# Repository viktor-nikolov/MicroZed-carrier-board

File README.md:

# MicroZed development carrier board

This repository provides KiCad design and production files for a [MicroZed](https://www.avnet.com/wps/portal/us/products/avnet-boards/avnet-board-families/microzed/) development carrier board (a.k.a. MicroZed carrier card).

### Please see [the repository's Wiki](https://github.com/viktor-nikolov/MicroZed-carrier-board/wiki) for details.

You are welcome to leave feedback in [the discussion](https://github.com/viktor-nikolov/MicroZed-carrier-board/discussions).

#### List of features:

- 106 digital I/O pins exposed via female headers
  
  - 16 I/O pins work on 5 V (exposed via two PMOD headers), and the rest of the pins work on 3.3 V

- 2 dedicated analog input pins XADC VP/VN

- 2 LEDs

- 2 push buttons

- 50 MHz precision oscillator (intended as an external clock input to the FPGA Programmable Logic)

- UART to USB conversion chip with the micro-USB connector (intended to enable UART communication for the FPGA Programmable Logic)

- Power input via micro-USB connector or screw terminal. On board power switch.

- Compatible with both [MicroZed 7010](https://www.avnet.com/shop/us/products/avnet-engineering-services/aes-z7mb-7z010-som-g-rev-h-3074457345644698173/?INTCMP=AMER-ECOMM-AVNET-BOARDS-AVT-INT-WEB-MICROZED-PRODUCTS-08282021) and [MicroZed 7020](https://www.avnet.com/shop/us/products/avnet-engineering-services/aes-z7mb-7z020-som-g-rev-h-3074457345644698177/?INTCMP=AMER-ECOMM-AVNET-BOARDS-AVT-INT-WEB-MICROZED-PRODUCTS-08282021).

&nbsp;

See other photos [here](pictures).

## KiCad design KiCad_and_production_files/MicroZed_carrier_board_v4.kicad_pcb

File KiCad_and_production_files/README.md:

# KiCad design files and production files

### Please see [the repository's Wiki](https://github.com/viktor-nikolov/MicroZed-carrier-board/wiki/1.-Board-design) for details.

I designed the board in [KiCad 7.0](https://www.kicad.org/).

> [!IMPORTANT]
> 
> I designed the board from the very beginning with the intention to manufacture it using [JLCPCB Manufacturing and Assembly](https://jlcpcb.com/capabilities/pcb-assembly-capabilities). (I'm not affiliated with JLCPCB in any way. I'm just their customer. :smiley:). The production files in this repository are ready for ordering manufacturing and assembly from JLCPCB. 
> 
> The manufacture of this board is not exactly cheap. Production of the final revision of the board (2 assembled boards + 3 spare PCBs) cost me $194 + shipping costs. (However you can save $33 if you exclude the [50 MHz oscillator X1](https://jlcpcb.com/partdetail/Xtaltq-NT0503DH3I507BN50/C2920832) from the assembly.)
> 
> My selection of parts was dictated by the availability of suitable parts in the [JLCPCB Assembly Parts Library](http://jlcpcb.com/parts) as of August 2023.
> 
> Some parts are tiny and have pads on the bottom. You would need a reflow oven or a hot plate for DIY assembly.

See the [list of all parts](MicroZed_carrier_board_v4_parts.pdf) used in the design (also provided as [an Excel file](MicroZed_carrier_board_v4_parts.xlsx))

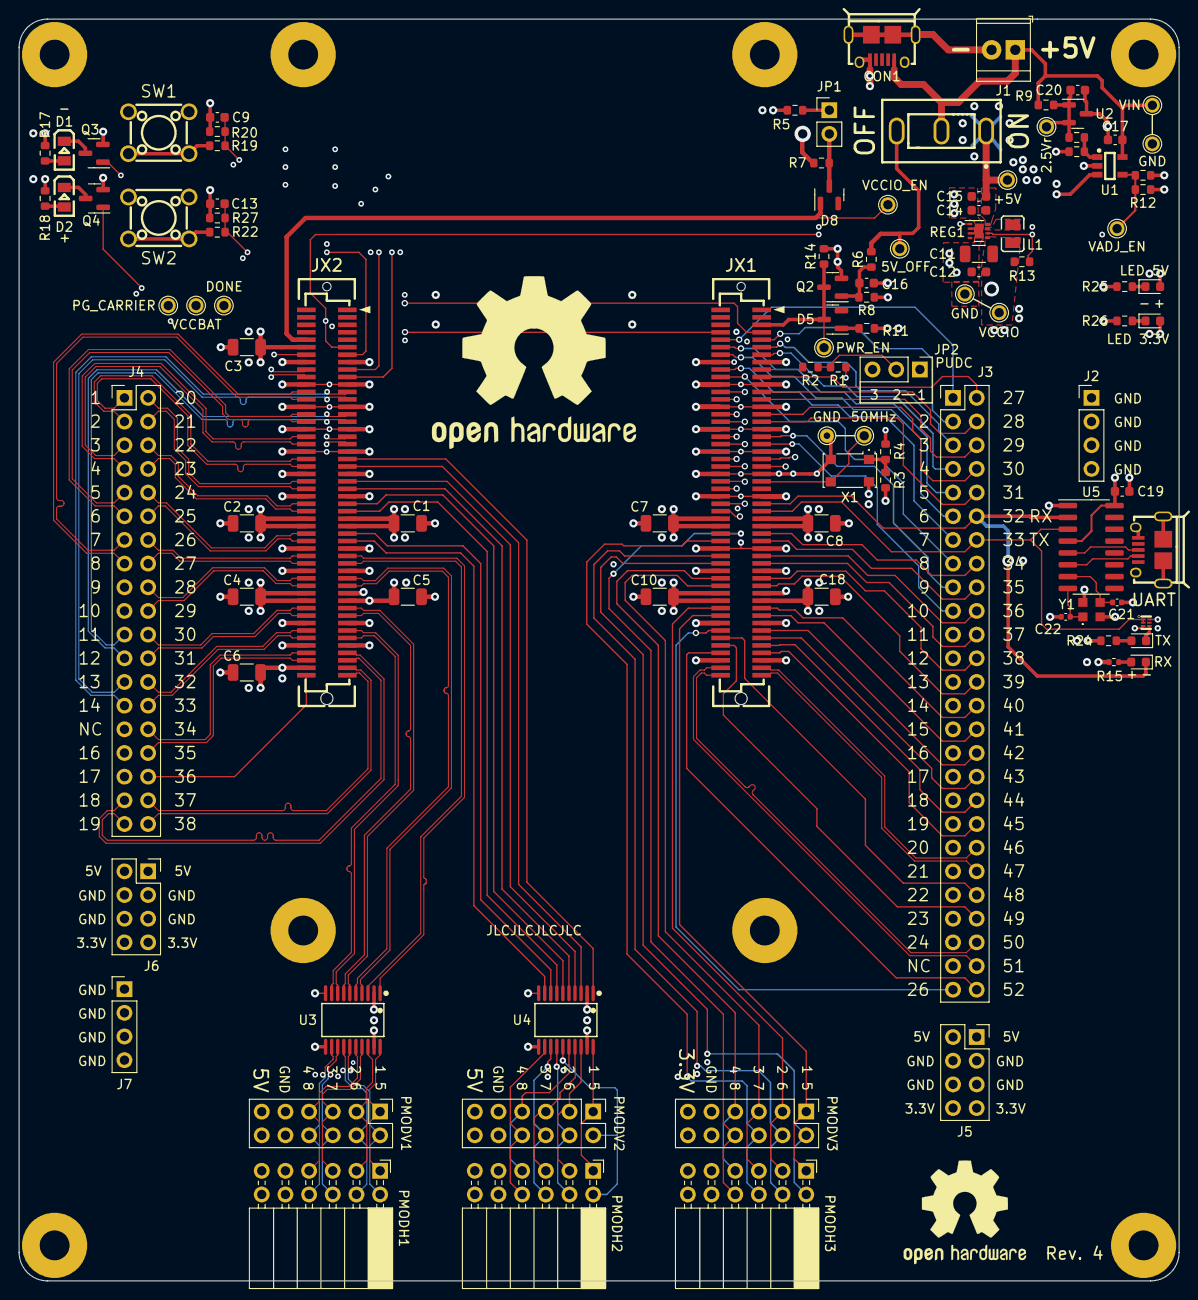
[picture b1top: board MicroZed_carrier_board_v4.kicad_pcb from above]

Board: 6 copper layers, 124.5 x 135.4 mm, 116 parts (0 on the bottom side), 169 nets.

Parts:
C1, C11: 22uF 10V; C_1206_3216Metric
C2, C3, C4, C5, C6, C7, C8, C10, C18: 22uF; C_1206_3216Metric
C9, C12, C13, C15, C16, C17, C19, C20: 100nF; C_0603_1608Metric
C14: 10uF 10V; C_0603_1608Metric
C21, C22: 22pF; C_0402_1005Metric
CON1: USB_B_Micro; MICRO-USB-SMD_HRS-ZX62D-B-5P830
CON2: UART; MICRO-USB-SMD_HRS-ZX62D-B-5P830
D1, D2: LED yellow; LED0805
D3, D4: LED green; LED_0603_1608Metric
D5, D8: BAT54C; SOT-23
D6: RX; LED_0603_1608Metric
D7: TX; LED_0603_1608Metric
H1, H2, H3, H4, H5, H6, H7, H8: MountingHole_3.2mm_Pad_7mm
J1: Screw_Terminal_01x02; TerminalBlock_TE_282834-2_1x02_P2.54mm_Horizontal
J2, J7: GND header for probes; PinHeader_1x04_P2.54mm_Vertical
J3: Conn_02x26_Top_Bottom; PinSocket_2x26_P2.54mm_Top_Bottom_nums
J4: Conn_02x19_Top_Bottom; PinSocket_2x19_P2.54mm_Top_Bottom_nums
J5, J6: Power Connector; PinSocket_2x04_P2.54mm_Vertical
JP1: Jumper_2_Open; PinHeader_1x02_P2.54mm_Vertical
JP2: PUDC selection; PinHeader_1x03_P2.54mm_Vertical
JX1, JX2: BergStak-100pos-plug-61083-101400
L1: 1uH 2A; Inductor-0806_L2.0-W1.6-1
OSHW-Logo: OSHW-Logo2_14.6x12mm_SilkScreen
OpenHW logo: OSHW-Logo2_24.3x20mm_SilkScreen
PMODH1, PMODH2, PMODH3: PMOD_Socket_Horizontal
PMODV1, PMODV2, PMODV3: PMOD_Socket_Vertical
Q2, Q3, Q4: BSS138; SOT-23
R1, R5, R6, R9: 1K; R_0603_1608Metric
R2, R19, R22: 100R; R_0603_1608Metric
R3: 220R 1%; R_0603_1608Metric
R4: 300R 1%; R_0603_1608Metric
R7: 10K; R_0603_1608Metric
R8: 3K92 1%; R_0603_1608Metric
R10: 1K5 1%; R_0603_1608Metric
R11, R16: 680R 1%; R_0603_1608Metric
R12: 3K; R_0603_1608Metric
R13: 180k; R_0603_1608Metric
R14: 430R 1%; R_0603_1608Metric
R15: 133R; R_0402_1005Metric
R17, R18: 150R; R_0603_1608Metric
R20, R27: 3K3; R_0603_1608Metric
R23: 100K; R_0603_1608Metric
R24: 154R; R_0603_1608Metric
R25: 4K87; R_0603_1608Metric
R26: 1K54; R_0603_1608Metric
REG1: TPS62082DSGR; WSON-8-1EP_2x2mm_P0.5mm_EP0.9x1.6mm
SW1, SW2: SW_MEC_5E; Switch-TH_4P-L6.0-W6.0-P4.50-LS6.5
SW3: SW_SPDT; Switch_SS12D10G4
TP1: VIN; TestPoint__Drill1.0mm
TP2, TP14: GND; TestPoint__Drill1.0mm
TP3: 2.5Vr; TestPoint__Drill1.0mm
TP4: +5V; TestPoint__Drill1.0mm
TP5: PWR_EN; TestPoint__Drill1.0mm
TP6: 5V_OFF; TestPoint__Drill1.0mm
TP7: VCCIO_EN; TestPoint__Drill1.0mm
TP8: VADJ_EN; TestPoint__Drill1.0mm
TP9: VCCIO; TestPoint__Drill1.0mm
TP10: PG_CARRIER; TestPoint__Drill1.0mm
TP11: VCCBAT; TestPoint__Drill1.0mm
TP12: DONE; TestPoint__Drill1.0mm
TP13: 50MHz; TestPoint__Drill1.0mm
TP16: GND; TestPoint_THTPad_D1.5mm_Drill0.7mm
U1: AP331A; SOT-25-5_L3.0-W1.8-P0.95-LS3.0-BR
U2: TL431A PJSEMI; SOT-23
U3, U4: TXB0108PWR; TSSOP-20_L6.5-W4.4-P0.65-LS6.4-BL
U5: CH340G; SOP-16_3.9x9.9mm_P1.27mm
U6: 74LVC1G08; X1-DFN1010-6_L1.0-W1.0-P0.35-BL
X1: NT0503DH3I507BN50; Oscillator_SMD_5.1x3.3mm
Y1: 12MHz; Crystal SMD2520-4P

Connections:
5V_OFF: R6.2, SW3.3 (C), TP6.1
+5V: C1.1, C2.1, C3.1, C7.1, C8.1, C14.1, C15.2, D3.2 (A), J5.1, J5.2, J6.1, J6.2, JX1.57 (VIN), JX1.58 (VIN), JX1.59 (VIN), JX1.60 (VIN), JX2.12 (VIN), JX2.57 (VIN), JX2.58 (VIN), JX2.59 (VIN), JX2.60 (VIN), PMODH1.10 (VCC), PMODH2.10 (VCC), PMODV1.10 (VCC), PMODV2.10 (VCC), R3.1, R5.2, R11.2, R12.1, REG1.8 (VIN), SW3.1 (A), TP4.1, U3.19 (VCCB), U4.19 (VCCB)
/2V5_REF: C20.1, R9.1, R10.1, TP3.1, U2.1 (REF), U2.2 (K)
/JX1_connections/IO_0: J3.2, JX1.9 (IO_0)
/JX1_connections/IO_25: J3.1, JX1.10 (IO_25)
/JX1_connections/IO_L1N: J3.4, JX1.13 (IO_L1N_T0)
/JX1_connections/IO_L1P: J3.3, JX1.11 (IO_L1P_T0)
/JX1_connections/IO_L2N: J3.6, JX1.14 (IO_L2N_T0)
/JX1_connections/IO_L2P: J3.5, JX1.12 (IO_L2P_T0)
/JX1_connections/IO_L3N: J3.27, JX1.19 (IO_L3N_T0_DQS)
/JX1_connections/IO_L4N: J3.8, JX1.20 (IO_L4N_T0)
/JX1_connections/IO_L4P: J3.7, JX1.18 (IO_L4P_T0)
/JX1_connections/IO_L5N: J3.29, JX1.25 (IO_L5N_T0)
/JX1_connections/IO_L5P: J3.28, JX1.23 (IO_L5P_T0)
/JX1_connections/IO_L6N: J3.12, JX1.26 (IO_L6N_T0_VREF)
/JX1_connections/IO_L6P: J3.11, JX1.24 (IO_L6P_T0)
/JX1_connections/IO_L7N: J3.31, JX1.31 (IO_L7N_T1)
/JX1_connections/IO_L7P: J3.30, JX1.29 (IO_L7P_T1)
/JX1_connections/IO_L8N: J3.14, JX1.32 (IO_L8N_T1)
/JX1_connections/IO_L8P: J3.13, JX1.30 (IO_L8P_T1)
/JX1_connections/IO_L9N: J3.10, JX1.37 (IO_L9N_T1_DQS)
/JX1_connections/IO_L9P: J3.9, JX1.35 (IO_L9P_T1_DQS)
/JX1_connections/IO_L10N: J3.18, JX1.38 (IO_L10N_T1)
/JX1_connections/IO_L10P: J3.17, JX1.36 (IO_L10P_T1)
/JX1_connections/IO_L11N: J3.16, JX1.43 (IO_L11N_T1_SRCC)
/JX1_connections/IO_L11N_13: J3.43, JX1.89 (IO_L11N_T1_SRCC_13)
/JX1_connections/IO_L11P: J3.15, JX1.41 (IO_L11P_T1_SRCC)
/JX1_connections/IO_L11P_13: J3.42, JX1.87 (IO_L11P_T1_SRCC_13)
/JX1_connections/IO_L12N: J3.20, JX1.44 (IO_L12N_T1_MRCC)
/JX1_connections/IO_L12N_13: J3.48, JX1.90 (IO_L12N_T1_MRCC_13)
/JX1_connections/IO_L12P: J3.19, JX1.42 (IO_L12P_T1_MRCC)
/JX1_connections/IO_L12P_13: J3.26, JX1.88 (IO_L12P_T1_MRCC_13)
/JX1_connections/IO_L13P_T2_MRCC: JX1.47 (IO_L13P_T2_MRCC), TP13.1, X1.3 (OUT)
/JX1_connections/IO_L14N: J3.22, JX1.50 (IO_L14N_T2_SRCC)
/JX1_connections/IO_L14P: J3.21, JX1.48 (IO_L14P_T2_SRCC)
/JX1_connections/IO_L15N: J3.33, JX1.55 (IO_L15N_T2_DQS), U5.3 (RXD), U6.1 (A), U6.2 (B)
/JX1_connections/IO_L15N_13: J3.45, JX1.93 (IO_L15N_T2_DQS_13)
/JX1_connections/IO_L15P: D6.1 (K), J3.32, JX1.53 (IO_L15P_T2_DQS), U5.2 (TXD)
/JX1_connections/IO_L15P_13: J3.44, JX1.91 (IO_L15P_T2_DQS_13)
/JX1_connections/IO_L16N: J3.24, JX1.56 (IO_L16N_T2)
/JX1_connections/IO_L16P: J3.23, JX1.54 (IO_L16P_T2)
/JX1_connections/IO_L17N: J3.35, JX1.63 (IO_L17N_T2)
/JX1_connections/IO_L17P: J3.34, JX1.61 (IO_L17P_T2)
/JX1_connections/IO_L18N: JX1.64 (IO_L18N_T2), PMODH3.7 (IO7), PMODV3.7 (IO7)
/JX1_connections/IO_L18P: JX1.62 (IO_L18P_T2), PMODH3.8 (IO8), PMODV3.8 (IO8)
/JX1_connections/IO_L19N: J3.37, JX1.69 (IO_L19N_T3_VREF)
/JX1_connections/IO_L19N_13: J3.52, JX1.94 (IO_L19N_T3_VREF_13)
/JX1_connections/IO_L19P: J3.36, JX1.67 (IO_L19P_T3)
/JX1_connections/IO_L19P_13: J3.49, JX1.92 (IO_L19P_T3_13)
/JX1_connections/IO_L20N: JX1.70 (IO_L20N_T3), PMODH3.5 (IO5), PMODV3.5 (IO5)
/JX1_connections/IO_L20P: JX1.68 (IO_L20P_T3), PMODH3.6 (IO6), PMODV3.6 (IO6)
/JX1_connections/IO_L21N: J3.39, JX1.75 (IO_L21N_T3_DQS)
/JX1_connections/IO_L21P: J3.38, JX1.73 (IO_L21P_T3_DQS)
/JX1_connections/IO_L22N: JX1.76 (IO_L22N_T3), PMODH3.3 (IO3), PMODV3.3 (IO3)
/JX1_connections/IO_L22P: JX1.74 (IO_L22P_T3), PMODH3.4 (IO4), PMODV3.4 (IO4)
/JX1_connections/IO_L23N: J3.41, JX1.83 (IO_L23N_T3)
/JX1_connections/IO_L23P: J3.40, JX1.81 (IO_L23P_T3)
/JX1_connections/IO_L24N: JX1.84 (IO_L24N_T3), PMODH3.1 (IO1), PMODV3.1 (IO1)
/JX1_connections/IO_L24P: JX1.82 (IO_L24P_T3), PMODH3.2 (IO2), PMODV3.2 (IO2)
/JX1_connections/PUDC_B: JX1.17 (IO_L3P_T0_DQS_PUDC_B), R2.2
/JX1_connections/UART to USB/USB_D+: CON2.3 (D+), U5.5 (UD+)
/JX1_connections/UART to USB/USB_D-: CON2.2 (D-), U5.6 (UD-)
/JX1_connections/XADC_DXN: J3.50, JX1.100 (XADC_DXN)
/JX1_connections/XADC_DXP: J3.51, JX1.98 (XADC_DXP)
/JX1_connections/XADC_VN: J3.47, JX1.99 (XADC_VN)
/JX1_connections/XADC_VP: J3.46, JX1.97 (XADC_VP)
/JX2_connections/IO_L2N: J4.9, JX2.20 (IO_L2N_T0_AD8N)
/JX2_connections/IO_L2P: J4.10, JX2.18 (IO_L2P_T0_AD8P)
/JX2_connections/IO_L3N: J4.13, JX2.25 (IO_L3N_T0_DQS_AD1N)
/JX2_connections/IO_L3P: J4.14, JX2.23 (IO_L3P_T0_DQS_AD1P)
/JX2_connections/IO_L4N: J4.7, JX2.26 (IO_L4N_T0)
/JX2_connections/IO_L4P: J4.8, JX2.24 (IO_L4P_T0)
/JX2_connections/IO_L5N: J4.11, JX2.31 (IO_L5N_T0_AD9N)
/JX2_connections/IO_L5P: J4.12, JX2.29 (IO_L5P_T0_AD9P)
/JX2_connections/IO_L6N: J4.5, JX2.32 (IO_L6N_T0_VREF)
/JX2_connections/IO_L6N_13: J4.36, JX2.100 (IO_L6N_T0_VREF_13)
/JX2_connections/IO_L6P: J4.6, JX2.30 (IO_L6P_T0)
/JX2_connections/IO_L7N: J4.3, JX2.38 (IO_L7N_T1_AD2N)
/JX2_connections/IO_L7P: J4.4, JX2.36 (IO_L7P_T1_AD2P)
/JX2_connections/IO_L8N: JX2.43 (IO_L8N_T1_AD10N), U4.3 (A2)
/JX2_connections/IO_L8P: JX2.41 (IO_L8P_T1_AD10P), U4.1 (A1)
/JX2_connections/IO_L9N: J4.16, JX2.37 (IO_L9N_T1_DQS_AD3N)
/JX2_connections/IO_L9P: J4.17, JX2.35 (IO_L9P_T1_DQS_AD3P)
/JX2_connections/IO_L10N: J4.1, JX2.44 (IO_L10N_T1_AD11N)
/JX2_connections/IO_L10P: J4.2, JX2.42 (IO_L10P_T1_AD11P)
/JX2_connections/IO_L11N: JX2.49 (IO_L11N_T1_SRCC), U4.5 (A4)
/JX2_connections/IO_L11P: JX2.47 (IO_L11P_T1_SRCC), U4.4 (A3)
/JX2_connections/IO_L12N: J4.21, JX2.50 (IO_L12N_T1_MRCC)
/JX2_connections/IO_L12P: J4.20, JX2.48 (IO_L12P_T1_MRCC)
/JX2_connections/IO_L13N: JX2.55 (IO_L13N_T2_MRCC), U4.7 (A6)
/JX2_connections/IO_L13P: JX2.53 (IO_L13P_T2_MRCC), U4.6 (A5)
/JX2_connections/IO_L14N: J4.23, JX2.56 (IO_L14N_T2_AD4N_SRCC)
/JX2_connections/IO_L14P: J4.22, JX2.54 (IO_L14P_T2_AD4P_SRCC)
/JX2_connections/IO_L15N: J4.25, JX2.64 (IO_L15N_T2_DQS_AD12N)
/JX2_connections/IO_L15P: J4.24, JX2.62 (IO_L15P_T2_DQS_AD12P)
/JX2_connections/IO_L16N: JX2.63 (IO_L16N_T2), U4.9 (A8)
/JX2_connections/IO_L16P: JX2.61 (IO_L16P_T2), U4.8 (A7)
/JX2_connections/IO_L17N: J4.27, JX2.70 (IO_L17N_T2_AD5N)
/JX2_connections/IO_L17P: J4.26, JX2.68 (IO_L17P_T2_AD5P)
/JX2_connections/IO_L18N: JX2.69 (IO_L18N_T2_AD13N), U3.3 (A2)
/JX2_connections/IO_L18P: JX2.67 (IO_L18P_T2_AD13P), U3.1 (A1)
/JX2_connections/IO_L19N: J4.29, JX2.76 (IO_L19N_T3_VREF)
/JX2_connections/IO_L19P: J4.28, JX2.74 (IO_L19P_T3)
/JX2_connections/IO_L20N: JX2.75 (IO_L20N_T3_AD6N), U3.5 (A4)
/JX2_connections/IO_L20P: JX2.73 (IO_L20P_T3_AD6P), U3.4 (A3)
/JX2_connections/IO_L20_13_N: J4.19, JX2.95 (IO_L20N_T3_13)
/JX2_connections/IO_L20_13_P: J4.18, JX2.93 (IO_L20P_T3_13)
/JX2_connections/IO_L21N: JX2.83 (IO_L21N_T3_DQS_AD14N), U3.7 (A6)
/JX2_connections/IO_L21P: JX2.81 (IO_L21P_T3_DQS_AD14P), U3.6 (A5)
/JX2_connections/IO_L21_13_N: J4.35, JX2.96 (IO_L21N_T3_DQS_13)
/JX2_connections/IO_L21_13_P: J4.34, JX2.94 (IO_L21P_T3_DQS_13)
/JX2_connections/IO_L22N: J4.31, JX2.84 (IO_L22N_T3_AD7N)
/JX2_connections/IO_L22P: J4.30, JX2.82 (IO_L22P_T3_AD7P)
/JX2_connections/IO_L22_13_N: J4.37, JX2.99 (IO_L22N_T3_13)
/JX2_connections/IO_L22_13_P: J4.38, JX2.97 (IO_L22P_T3_13)
/JX2_connections/IO_L23N: JX2.89 (IO_L23N_T3), U3.9 (A8)
/JX2_connections/IO_L23P: JX2.87 (IO_L23P_T3), U3.8 (A7)
/JX2_connections/IO_L24N: J4.33, JX2.90 (IO_L24N_T3_AD15N)
/JX2_connections/IO_L24P: J4.32, JX2.88 (IO_L24P_T3_AD15P)
/JX2_connections/LED1: JX2.17 (IO_L1P_T0_AD0P), Q3.1 (G)
/JX2_connections/LED2: JX2.14 (IO_25), Q4.1 (G)
/JX2_connections/PMOD1 & PMOD2 connections/PMOD1_1N: PMODH1.2 (IO2), PMODV1.2 (IO2), U3.18 (B2)
/JX2_connections/PMOD1 & PMOD2 connections/PMOD1_1P: PMODH1.1 (IO1), PMODV1.1 (IO1), U3.20 (B1)
/JX2_connections/PMOD1 & PMOD2 connections/PMOD1_2N: PMODH1.4 (IO4), PMODV1.4 (IO4), U3.16 (B4)
/JX2_connections/PMOD1 & PMOD2 connections/PMOD1_2P: PMODH1.3 (IO3), PMODV1.3 (IO3), U3.17 (B3)
/JX2_connections/PMOD1 & PMOD2 connections/PMOD1_3N: PMODH1.6 (IO6), PMODV1.6 (IO6), U3.14 (B6)
/JX2_connections/PMOD1 & PMOD2 connections/PMOD1_3P: PMODH1.5 (IO5), PMODV1.5 (IO5), U3.15 (B5)
/JX2_connections/PMOD1 & PMOD2 connections/PMOD1_4N: PMODH1.8 (IO8), PMODV1.8 (IO8), U3.12 (B8)
/JX2_connections/PMOD1 & PMOD2 connections/PMOD1_4P: PMODH1.7 (IO7), PMODV1.7 (IO7), U3.13 (B7)
/JX2_connections/PMOD1 & PMOD2 connections/PMOD2_B1: PMODH2.1 (IO1), PMODV2.1 (IO1), U4.20 (B1)
/JX2_connections/PMOD1 & PMOD2 connections/PMOD2_B2: PMODH2.2 (IO2), PMODV2.2 (IO2), U4.18 (B2)
/JX2_connections/PMOD1 & PMOD2 connections/PMOD2_B3: PMODH2.3 (IO3), PMODV2.3 (IO3), U4.17 (B3)
/JX2_connections/PMOD1 & PMOD2 connections/PMOD2_B4: PMODH2.4 (IO4), PMODV2.4 (IO4), U4.16 (B4)
/JX2_connections/PMOD1 & PMOD2 connections/PMOD2_B5: PMODH2.5 (IO5), PMODV2.5 (IO5), U4.15 (B5)
/JX2_connections/PMOD1 & PMOD2 connections/PMOD2_B6: PMODH2.6 (IO6), PMODV2.6 (IO6), U4.14 (B6)
/JX2_connections/PMOD1 & PMOD2 connections/PMOD2_B7: PMODH2.7 (IO7), PMODV2.7 (IO7), U4.13 (B7)
/JX2_connections/PMOD1 & PMOD2 connections/PMOD2_B8: PMODH2.8 (IO8), PMODV2.8 (IO8), U4.12 (B8)
/JX2_connections/SWITCH1: C9.1, JX2.19 (IO_L1N_T0_AD0N), R19.1, R20.1
/JX2_connections/SWITCH2: C13.1, JX2.13 (IO_0), R22.1, R27.1
/VADJ_EN: R12.2, R23.1, REG1.1 (EN), TP8.1, U1.4
GND: C1.2, C2.2, C3.2, C4.2, C5.1, C6.2, C7.2, C8.2, C9.2, C10.2, C11.1, C12.2, C13.2, C14.2, C15.1, C16.2, C17.2, C18.2, C19.1, C20.2, C21.2, C22.2, CON1.5 (GND), CON1.6 (Shield), CON1.7 (Shield), CON1.8 (Shield), CON1.9 (Shield), CON2.5 (GND), CON2.6 (Shield), CON2.7 (Shield), CON2.8 (Shield), CON2.9 (Shield), J1.2, J2.1, J2.2, J2.3, J2.4, J5.3, J5.4, J5.5, J5.6, J6.3, J6.4, J6.5, J6.6, J7.1, J7.2, J7.3, J7.4, JP2.3 (B), JX1.15 (GND), JX1.16 (GND), JX1.21 (GND), JX1.22 (GND), JX1.27 (GND), JX1.28 (GND), JX1.33 (GND), JX1.34 (GND), JX1.39 (GND), JX1.40 (GND), JX1.45 (GND), JX1.46 (GND), JX1.51 (GND), JX1.52 (GND), JX1.65 (GND), JX1.66 (GND), JX1.71 (GND), JX1.72 (GND), JX1.77 (GND), JX1.85 (GND), JX1.86 (GND), JX1.95 (GND), JX1.96 (GND), JX2.15 (GND), JX2.16 (GND), JX2.21 (GND), JX2.22 (GND), JX2.27 (GND), JX2.28 (GND), JX2.33 (GND), JX2.34 (GND), JX2.39 (GND), JX2.40 (GND), JX2.45 (GND), JX2.46 (GND), JX2.51 (GND), JX2.52 (GND), JX2.65 (GND), JX2.66 (GND), JX2.71 (GND), JX2.72 (GND), JX2.77 (GND), JX2.85 (GND), JX2.86 (GND), JX2.91 (GND), JX2.92 (GND), PMODH1.9 (GND), PMODH2.9 (GND), PMODH3.9 (GND), PMODV1.9 (GND), PMODV2.9 (GND), PMODV3.9 (GND), Q2.2 (S), Q3.2 (S), Q4.2 (S), R4.2, R7.2, R8.1, R14.2, R16.2, R20.2, R23.2, R25.2, R26.2, R27.2, REG1.2 (GND), REG1.3 (MODE), REG1.9 (pad), TP2.1, TP14.1, TP16.1, U1.2 (V-), U2.3 (A), U3.11 (GND), U4.11 (GND), U5.1 (GND), U6.3 (GND), X1.2 (GND), Y1.2, Y1.4
unnamed: D1.2 (A), R17.2
unnamed: D1.1 (K), Q3.3 (D)
unnamed: D2.2 (A), R18.2
unnamed: D2.1 (K), Q4.3 (D)
unnamed: D3.1 (K), R25.1
unnamed: D4.1 (K), R26.1
unnamed: D5.1, R11.1
unnamed: D6.2 (A), R15.2
unnamed: D7.2 (A), R24.2
unnamed: D7.1 (K), U6.4 (Y)
unnamed: JP1.1 (A), R5.1
unnamed: D8.3, JP1.2 (B), R7.1, U1.3 (+)
unnamed: JP2.2 (C), R1.1, R2.1
unnamed: JX1.8 (DONE), TP12.1
unnamed: JX1.7 (VCCBATT), TP11.1
unnamed: C16.1, Q2.1 (G), R6.1, R8.2
unnamed: L1.1, REG1.7 (SW)
unnamed: R19.2, SW1.3 (K), SW1.4 (A)
unnamed: R22.2, SW2.3 (K), SW2.4 (A)
unnamed: R10.2, R16.1, U1.1 (-)
unnamed: C21.1, U5.7 (XI), Y1.3
unnamed: C22.1, U5.8 (XO), Y1.1
unnamed: R3.2, R4.1, X1.1 (Vctrl)
PG_CARRIER: JX2.11 (PG_CARRIER), R13.1, REG1.6 (PG), TP10.1
PWR_EN: D5.3, JX1.5 (PWR_EN), Q2.3 (D), R14.1, TP5.1
VCCIO: C4.1, C5.2, C6.1, C10.1, C11.2, C12.1, C18.1, C19.2, D4.2 (A), J5.7, J5.8, J6.7, J6.8, JX1.78 (VCCIO_34), JX1.79 (VCCIO_34), JX1.80 (VCCIO_34), JX2.78 (VCCIO_35), JX2.79 (VCCIO_35), JX2.80 (VCCIO_35), JX2.98 (VCCO_13), L1.2, PMODH3.10 (VCC), PMODV3.10 (VCC), R1.2, R13.2, R15.1, R17.1, R18.1, R24.1, REG1.5 (VOS), SW1.1, SW1.2, SW2.1, SW2.2, TP9.1, U3.2 (VCCA), U3.10 (OE), U4.2 (VCCA), U4.10 (OE), U5.4 (V3), U5.16 (VCC), U6.6 (VCC), X1.4 (V+)
VCCIO_EN: D8.1, JX2.10 (VCCIO_EN), TP7.1
VIN: C17.1, CON1.1 (VBUS), J1.1, R9.2, SW3.2 (B), TP1.1, U1.5 (V+)

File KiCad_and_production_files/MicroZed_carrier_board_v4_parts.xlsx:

Comment | Designator | Footprint | LCSC Part No | Manuf. Part No | Comment
USB micro connector | CON1, CON2 |  | C719023 | ZX62D-B-5P8(30)
tactile switch | SW1,SW2 |  | C445493 | K2-1102DP-L3SW-04
on/off switch | SW3 |  | C2887259 | SS12D10G4 071
100nF | C9,C12,C13,C15,C16,C17,C19,C20 | 0603 | C66501 | CC0603KRX7R9BB104
22uF | C1,C2,C3,C4,C5,C6,C7,C8,C10,C11,C18 | 1206 | C5672 | CL31A226KPHNNNE
10uF | C14 | 0603 | C19702 | CL10A106KP8NNNC
DC-DC 3.3V 1.2A | REG1 | DFN-8-EP(2x2) | C485809 | TPS62082DSGR
2.6A 1uH ±20% 4.2A | L1 | 0806 | C2913752 | BDHH002016101R0MDB | datasheet of REG1 recommends XFL3012-102MEB, but that is not available in JLCPC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
MOSFET | Q2,Q3,Q4 | SOT-23 | C400505 | BSS138
3K92 1% | R8 | 0603 | C170585 | WR06X3921FTL
680R 1% | R11, R16 | 0603 | C23228 | 0603WAF6800T5E
430R 1% | R14 | 0603 | C23170 | 0603WAF4300T5E
1K 1% | R1,R5,R6,R9 | 0603 | C21190 | 0603WAF1001T5E
220R 1% | R3 | 0603 | C22962 | 0603WAF2200T5E
1.5K 1% | R10 | 0603 | C22843 | 0603WAF1501T5E
3K 1% | R12 | 0603 | C4211 | 0603WAF3001T5E
100K 1% | R23 | 0603 | C25803 | 0603WAF1003T5E
100R | R2,R19,R22 | 0603 | C22775 | 0603WAF1000T5E
300R | R4 | 0603 | C23025 | 0603WAF3000T5E
3.3K 1% | R20,R27 | 0603 | C22978 | 0603WAF3301T5E
180k | R13 | 0603 | C22827 | 0603WAF1803T5E
1K54 | R26 | 0603 | C100784 | CR0603FA1541G
10K | R7 | 0603 | C25804 | 0603WAF1002T5E
Shotky diode | D5, D8 | SOT-23 | C37704 | BAT54C,215
2.5V Ref | U2 | SOT-23-3 | C411753 | TL431A PJSEMI | warning: original TI part has diferent pinout!
comparator | U1 | SOT-25-5 | C151034 | AP331AWG-7
BergStak 100pos Plug height 4.7 mm | JX1,JX2 |  | C2764776 | 61083-101400LF
level shifter | U3,U4 | TSSOP-20 | C53406 | TXB0108PWR
4K87 | R25 | 0603 | C2097544 | MCT06030C4871FP500 | for green 5V indicator LED
PL LED yellow | D1,D2 | 0805 | C2296 | 17-21SUYC/TR8
150R 1% | R17,R18 | 0603 | C22808 | 0603WAF1500T5E | for yellow 3.3V indicator LED
±0.5ppm 50MHz oscillator | X1 |  | C2920832 | NT0503DH3I507BN50
Interface Chip USB/UART | U5 | SOP-16 | C14267 | CH340G | the same as used in https://www.sparkfun.com/products/14050
AND gate | U6 | X1-DFN1010-6 | C150443 | 74LVC1G08FW5-7
12MHz 15pF crystal | Y1 | SMD2520-4P | C2149206 | 2TJ412000UYGBC
22pF for crystal | C21,C22 | 0402 | C881987 | C0402C0G220J250NTB
LED green | D3,D4,D6 | 0603 | C2833058 | BZ-C0603-G3-F1 | power indicators, RX_to_FPGA
133R for green LED RX | R15 | 0402 | C4326496 | CRCW0402133RFKED
LED yellow for TX_from_FPGA | D7 | 0603 | C5151485 | A-SP192YY3C-A01-4T
154R for yellow LED | R24 | 0603 | C365385 | ETCR0603F154RK9
Following connectors are not part of BOM, i.e. not part of JLCPCB Assembly (the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
Comment | Designator |  |  | Manuf. Part No
38 pin header | J4 |  |  | SSW-119-01-F-D
52 pin header | J3 |  |  | SSQ-126-03-G-D
2 pin header, 6 mm | JP1 |  |  | 61300211121
PMOD receptacle right angle | PMODH1,PMODH2,PMODH3 |  |  | SSQ-106-03-T-D-RA
PMOD receptacle straight | PMODV1,PMODV2,PMODV3 |  |  | Farnell SSQ-106-01-G-D
Power connector 8 pin, 2 rows | J5,J6 |  |  | Farnell SSQ-104-02-G-D
GND header for probes, 4 pin, 1 row | J2, J7 |  |  | Farnell TSW-104-14-L-S

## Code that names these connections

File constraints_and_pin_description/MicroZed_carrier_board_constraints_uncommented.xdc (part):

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## - rename the used ports (in each line, after get_ports) according to the top level signal names in the project

############  LEDs and switches  ############
set_property -dict { PACKAGE_PIN C20 IOSTANDARD LVCMOS33 } [get_ports { LED1    }];
set_property -dict { PACKAGE_PIN J15 IOSTANDARD LVCMOS33 } [get_ports { LED2    }];
set_property -dict { PACKAGE_PIN B20 IOSTANDARD LVCMOS33 } [get_ports { SWITCH1 }];
set_property -dict { PACKAGE_PIN G14 IOSTANDARD LVCMOS33 } [get_ports { SWITCH2 }];

############  50 MHz oscillator input  ############
set_property -dict { PACKAGE_PIN N18 IOSTANDARD LVCMOS33 } [get_ports { OSC_50MHZ }];
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set_property -dict { PACKAGE_PIN  V7 IOSTANDARD LVCMOS33 } [get_ports { J3_43 }]; # MicroZed 7020 only
set_property -dict { PACKAGE_PIN  V8 IOSTANDARD LVCMOS33 } [get_ports { J3_44 }]; # MicroZed 7020 only
set_property -dict { PACKAGE_PIN  W8 IOSTANDARD LVCMOS33 } [get_ports { J3_45 }]; # MicroZed 7020 only
set_property         PACKAGE_PIN  K9                       [get_ports { J3_46 }]; # analog input XADC_VP
set_property         PACKAGE_PIN L10                       [get_ports { J3_47 }]; # analog input XADC_VN
set_property -dict { PACKAGE_PIN U10 IOSTANDARD LVCMOS33 } [get_ports { J3_48 }]; # MicroZed 7020 only
set_property -dict { PACKAGE_PIN  T5 IOSTANDARD LVCMOS33 } [get_ports { J3_49 }]; # MicroZed 7020 only
## J3_50 and J3_51 are temperature-sensing diode pins not usable by PL (see UG475, Table1-12)
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
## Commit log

2023-09-16 Constraints update
2023-09-17 Remove unneeded files
2023-09-17 Update of photos
2023-09-17 update of pictures
2023-09-18 picture updated
2023-09-22 Update list of parts
2023-09-23 Create files
2023-09-23 Rename folder
2023-09-23 Create LICENSE
2023-09-24 Remove folder
2023-09-24 Components rotation offsets added
2023-09-24 Update of license to CC0
2023-09-24 Create LICENSE for HW and SW
2023-10-09 Readme update

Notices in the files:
KiCad_and_production_files/MicroZed_carrier_board_v4.kicad_pcb:
License: Creative Commons Zero
(c) 2023 Viktor Nikolov
README.md:
License: CC0-1.0
